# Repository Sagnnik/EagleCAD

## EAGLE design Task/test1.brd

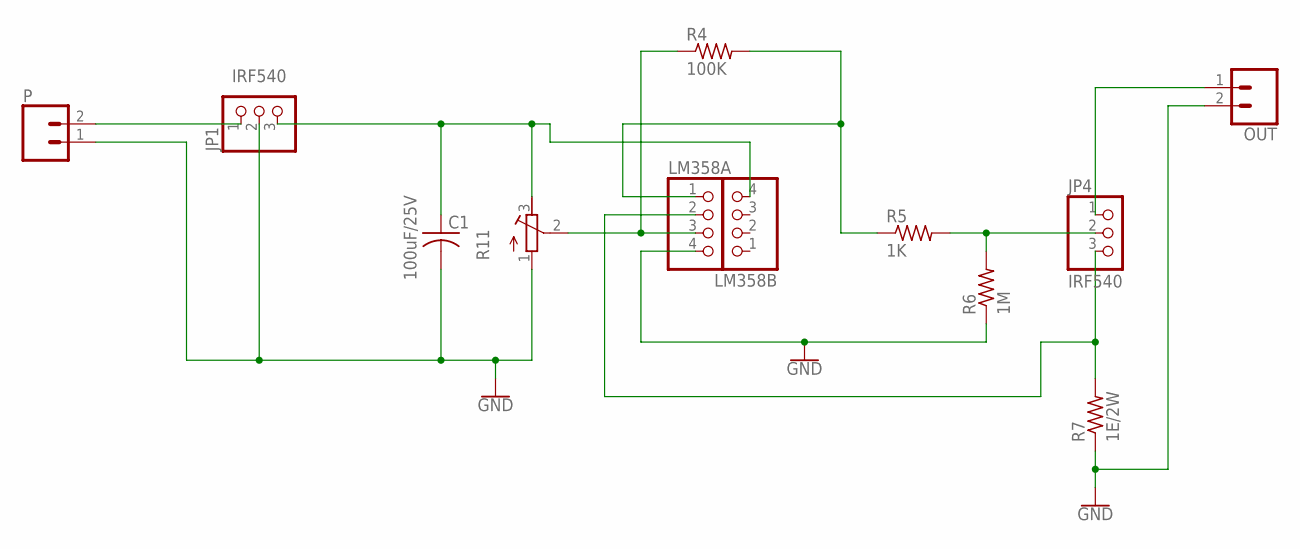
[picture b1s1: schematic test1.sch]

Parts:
C1: 100uF/25V; C025-024X044
JP1, JP4: IRF540; 1X03
LM358A, LM358B: PINHD-1X4; 1X04
OUT: CONN_02; 1X02
P: CONN_02; 1X02
R4: 100K; 0204/5
R5: 1K; 0204/5
R6: 1M; 0204/5
R7: 1E/2W; 0204/5
R11: R-TRIMM3339P; RTRIM3339P

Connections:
GND: C1.2, JP1.2, LM358A.4, OUT.2, P.1, R6.1, R7.1, R11.1 (A)
unnamed: JP1.1, P.2
unnamed: JP4.1, OUT.1
unnamed: JP4.3, LM358A.2, R7.2
unnamed: LM358A.3, R4.1, R11.2 (S)
unnamed: LM358A.1, R4.2, R5.1
unnamed: JP4.2, R5.2, R6.2
O1+: C1.1, JP1.3, LM358B.4, R11.3 (E)

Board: 2 copper layers, 12 parts (0 on the bottom side), 8 nets, no tracks yet.

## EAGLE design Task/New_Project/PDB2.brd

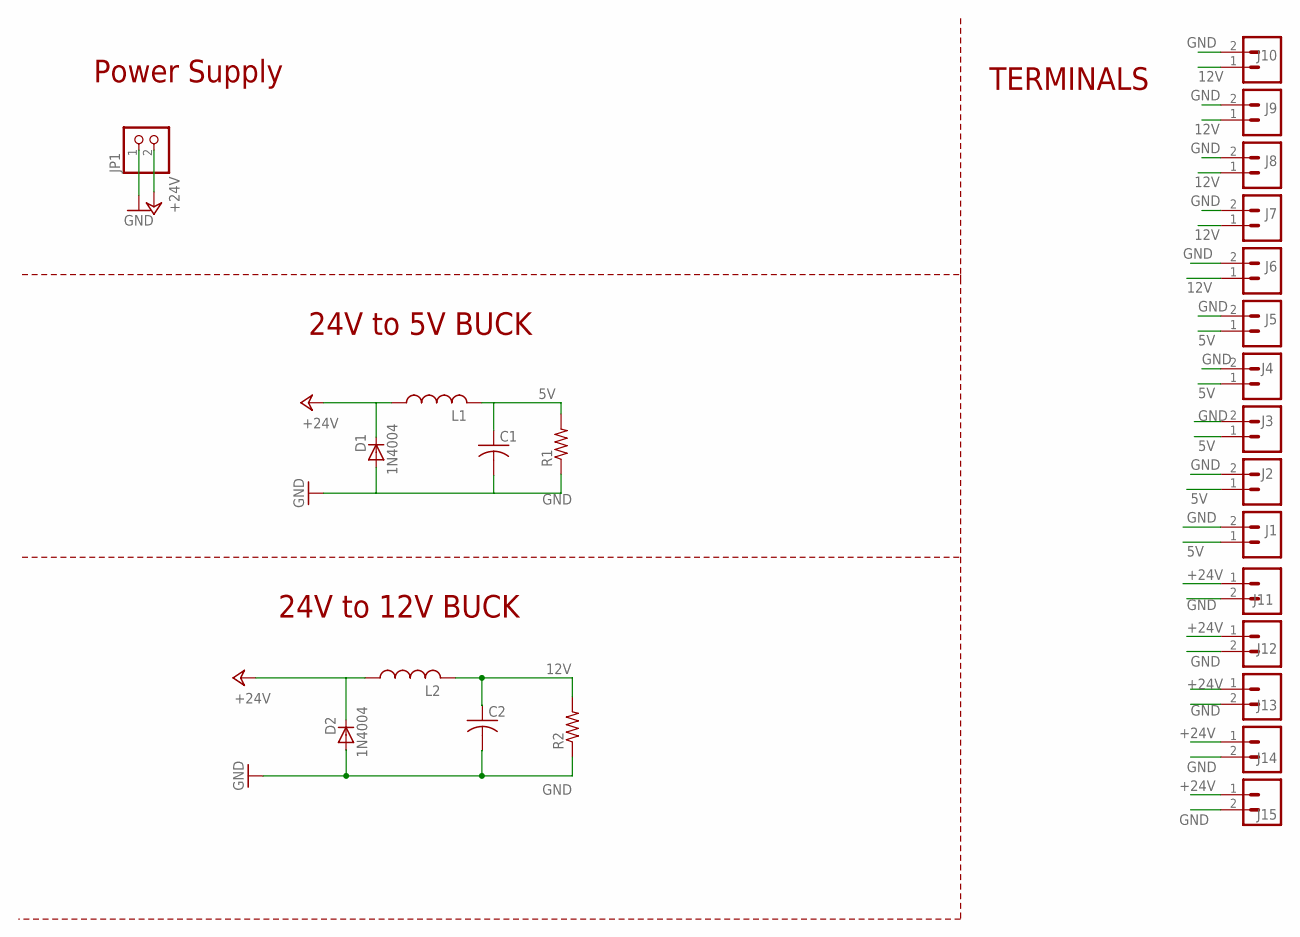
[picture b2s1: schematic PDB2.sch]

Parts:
C1, C2: C-US025-050X050; C025-050X050
D1, D2: 1N4004; DO41-10
J1, J2, J3, J4, J5, J6, J7, J8, J9, J10, J11, J12, J13, J14, J15: CONN_02; 1X02
JP1: PINHD-1X2; 1X02
L1, L2: L-US0207/7; 0207/7
R1, R2: R-US_0207/10; 0207/10

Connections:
5V: C1.1, J1.1, J2.1, J3.1, J4.1, J5.1, L1.2, R1.2
12V: C2.1, J6.1, J7.1, J8.1, J9.1, J10.1, L2.2, R2.2
+24V: D1.C, D2.C, J11.1, J12.1, J13.1, J14.1, J15.1, JP1.2, L1.1, L2.1
GND: C1.2, C2.2, D1.A, D2.A, J1.2, J2.2, J3.2, J4.2, J5.2, J6.2, J7.2, J8.2, J9.2, J10.2, J11.2, J12.2, J13.2, J14.2, J15.2, JP1.1, R1.1, R2.1

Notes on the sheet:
Power Supply
24V to 5V BUCK
24V to 12V BUCK
TERMINALS

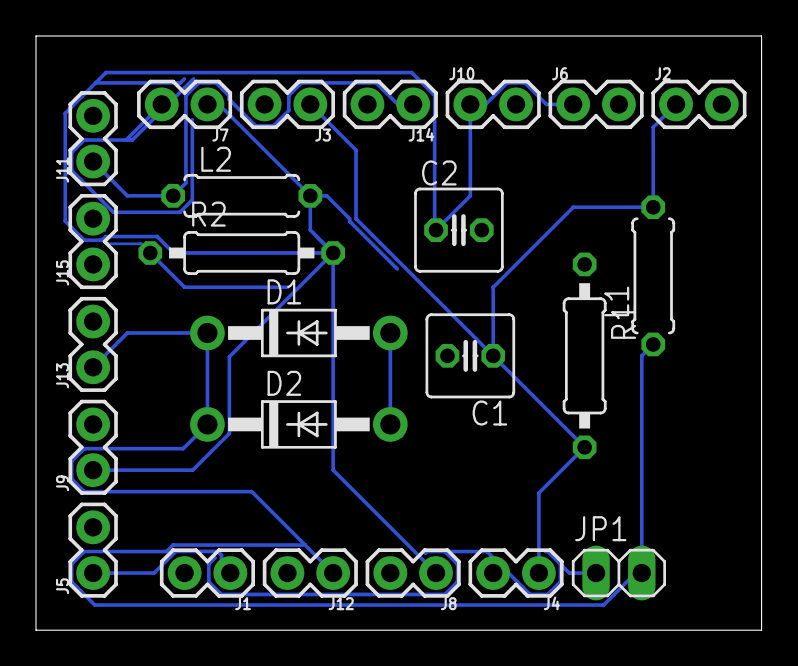
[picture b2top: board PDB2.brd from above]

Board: 2 copper layers, 40.3 x 33.0 mm, 24 parts (0 on the bottom side), 4 nets.

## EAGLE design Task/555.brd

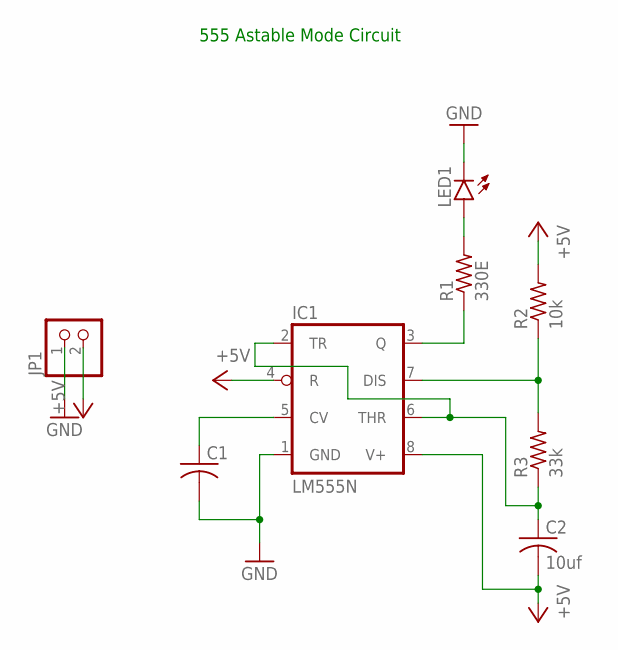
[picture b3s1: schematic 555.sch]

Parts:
C1: C-US025-024X044; C025-024X044
C2: 10uf; C025-024X044
IC1: LM555N; DIL08-ROUND
JP1: PINHD-1X2; 1X02
LED1: LED5MM
R1: 330E; 0204/7
R2: 10k; 0204/7
R3: 33k; 0204/7

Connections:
+5V: C2.2, IC1.4 (R), IC1.8 (V+), JP1.2, R2.2
GND: C1.2, IC1.1 (GND), JP1.1, LED1.K (C)
unnamed: LED1.A, R1.2
unnamed: IC1.3 (Q), R1.1
unnamed: IC1.7 (DIS), R2.1, R3.2
unnamed: C2.1, IC1.2 (TR), IC1.6 (THR), R3.1
unnamed: C1.1, IC1.5 (CV)

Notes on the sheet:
555 Astable Mode Circuit

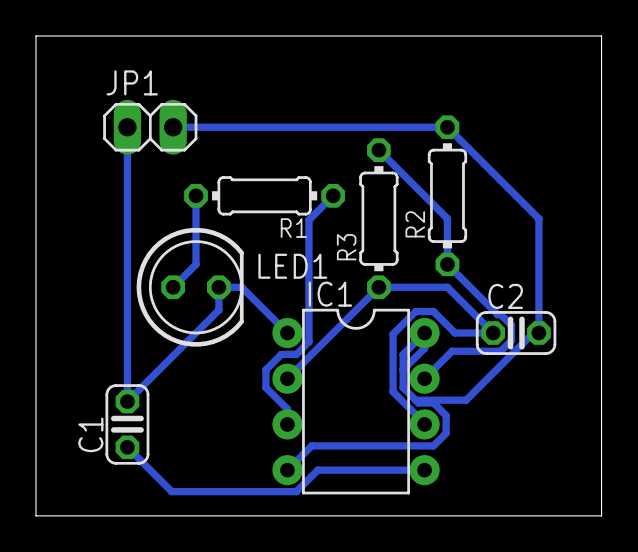
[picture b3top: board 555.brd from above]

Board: 2 copper layers, 31.4 x 26.7 mm, 8 parts (0 on the bottom side), 7 nets.

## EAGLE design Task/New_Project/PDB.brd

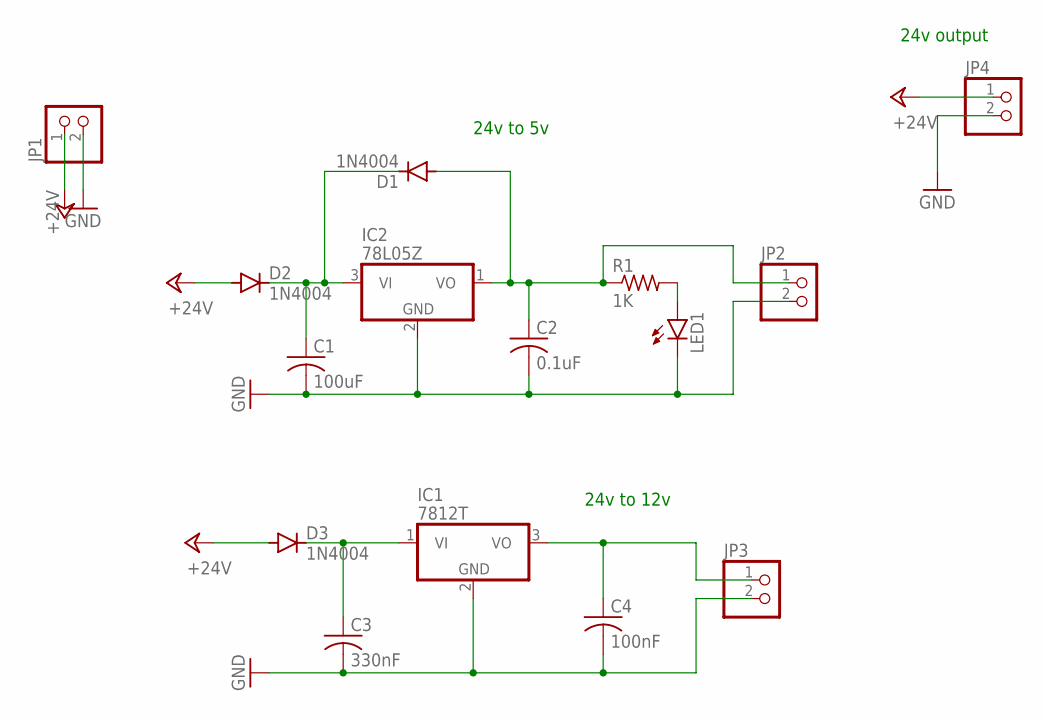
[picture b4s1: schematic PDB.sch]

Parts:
C1: 100uF; C025-024X044
C2: 0.1uF; C025-024X044
C3: 330nF; C025-024X044
C4: 100nF; C025-024X044
D1, D2, D3: 1N4004; DO41-10
IC1: 7812T; TO220H
IC2: 78L05Z; TO92
JP1, JP2, JP3, JP4: PINHD-1X2; 1X02
LED1: LED5MM
R1: 1K; 0204/7

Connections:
+24V: D2.A, D3.A, JP1.1, JP4.1
GND: C1.2, C2.2, C3.2, C4.2, IC1.2 (GND), IC2.2 (GND), JP1.2, JP2.2, JP3.2, JP4.2, LED1.K (C)
unnamed: C3.1, D3.C, IC1.1 (VI)
unnamed: C1.1, D1.C, D2.C, IC2.3 (VI)
unnamed: C2.1, D1.A, IC2.1 (VO), JP2.1, R1.1
unnamed: C4.1, IC1.3 (VO), JP3.1
unnamed: LED1.A, R1.2

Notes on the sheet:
24v to 5v
24v to 12v
24v output

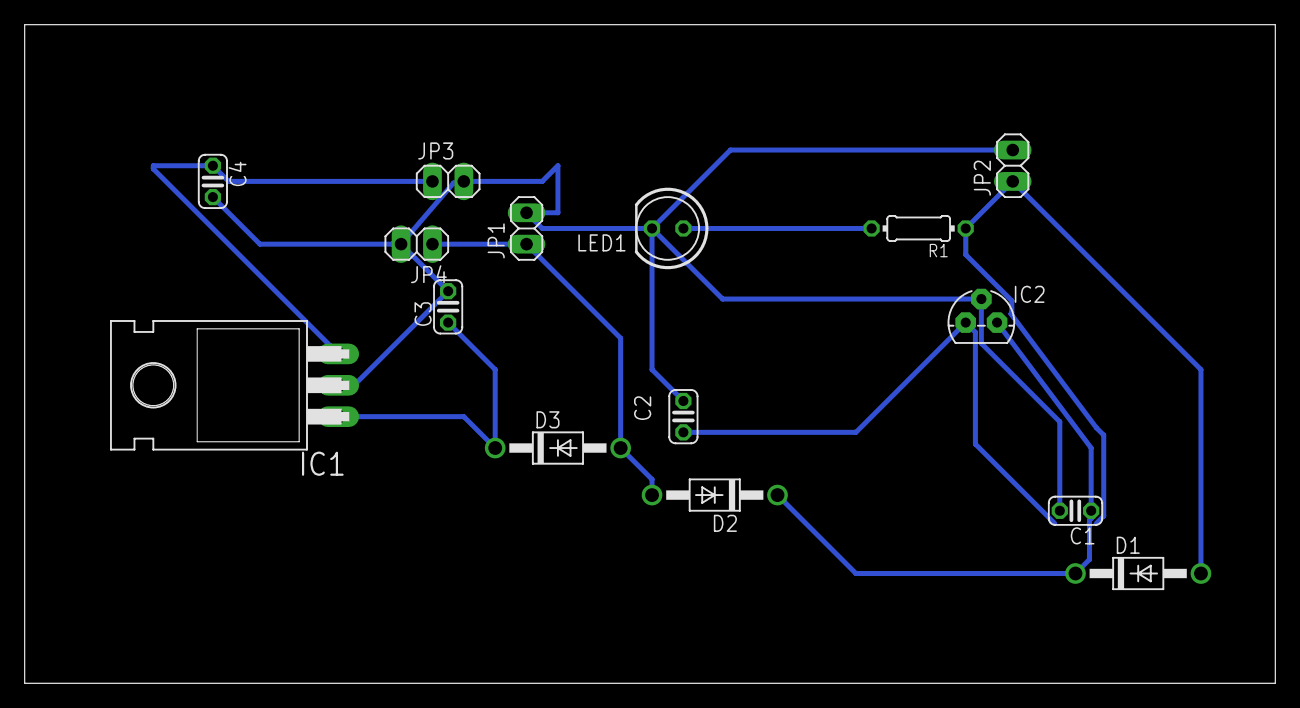
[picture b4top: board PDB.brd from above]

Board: 2 copper layers, 101.3 x 53.3 mm, 15 parts (0 on the bottom side), 7 nets.

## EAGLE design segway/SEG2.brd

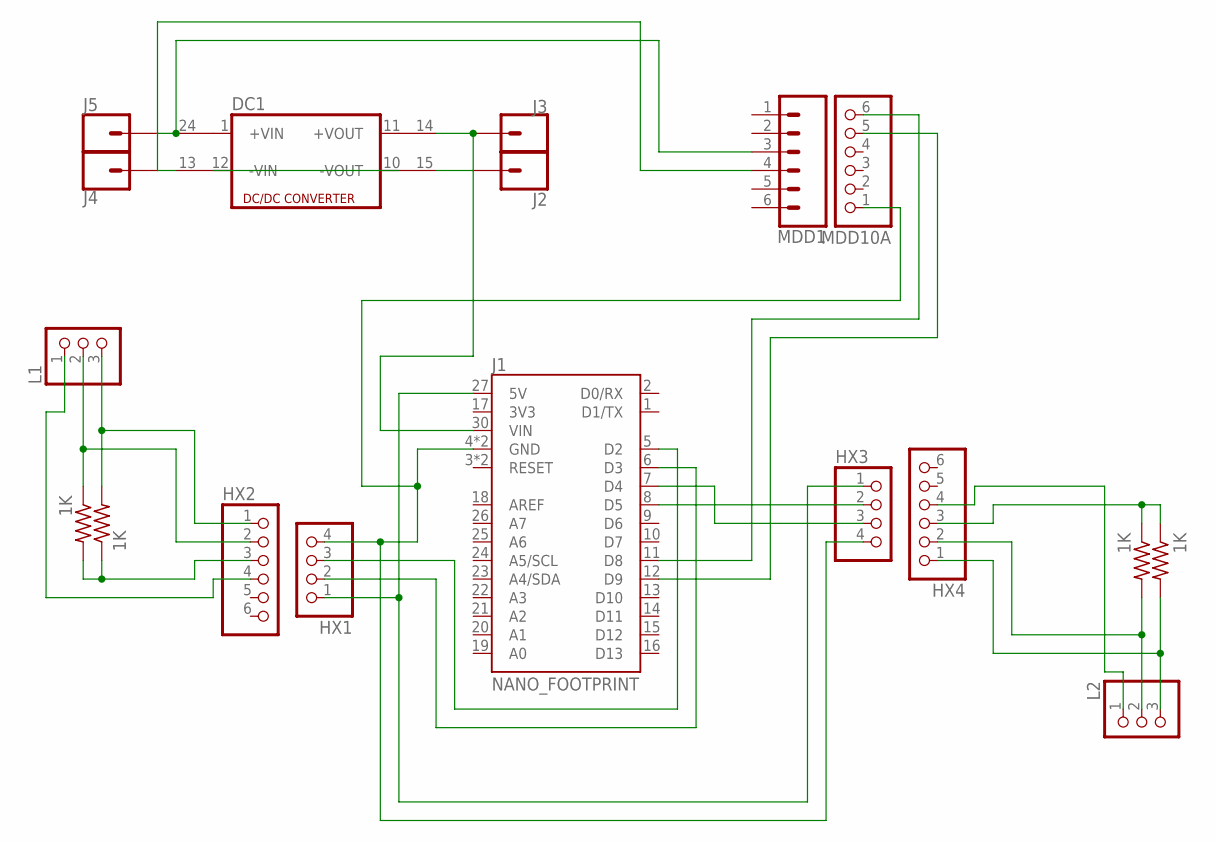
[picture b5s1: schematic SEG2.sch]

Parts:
DC1: DC213R; CMK
HX1, HX3: PINHD-1X4; 1X04
HX2, HX4: PINHD-1X6; 1X06
J1: NANO_FOOTPRINT; NANO
J2, J3, J4, J5: CONN_01; 1X01
L1, L2: PINHD-1X3; 1X03
MDD1: CONN_06LOCK; 1X06_LOCK
MDD10A: PINHD-1X6; 1X06
R1, R2, R3, R4: 1K; 0204/7

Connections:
unnamed: HX1.4, HX3.4, J1.4 (GND), J1.29 (GND), MDD10A.1
unnamed: HX1.3, J1.5 (D2)
unnamed: HX1.2, J1.6 (D3)
unnamed: HX1.1, HX3.1, J1.27 (5V)
unnamed: HX2.3, R1.1, R2.2
unnamed: HX3.3, J1.7 (D4)
unnamed: HX3.2, J1.8 (D5)
unnamed: HX2.2, L1.2, R2.1
unnamed: HX2.4, L1.1
unnamed: HX2.1, L1.3, R1.2
unnamed: HX4.1, L2.3, R3.2
unnamed: HX4.2, L2.2, R4.2
unnamed: DC1.24 (+VIN1), J4.1, MDD1.3
unnamed: HX4.3, R3.1, R4.1
unnamed: HX4.4, L2.1
unnamed: DC1.14 (+VOUT1), J1.30 (VIN), J2.1
unnamed: DC1.10 (-VOUT), DC1.12 (-VIN)
unnamed: DC1.13 (-VIN1), J5.1, MDD1.4
unnamed: DC1.15 (-VOUT1), J3.1
unnamed: J1.11 (D8), MDD10A.6
unnamed: J1.12 (D9), MDD10A.5

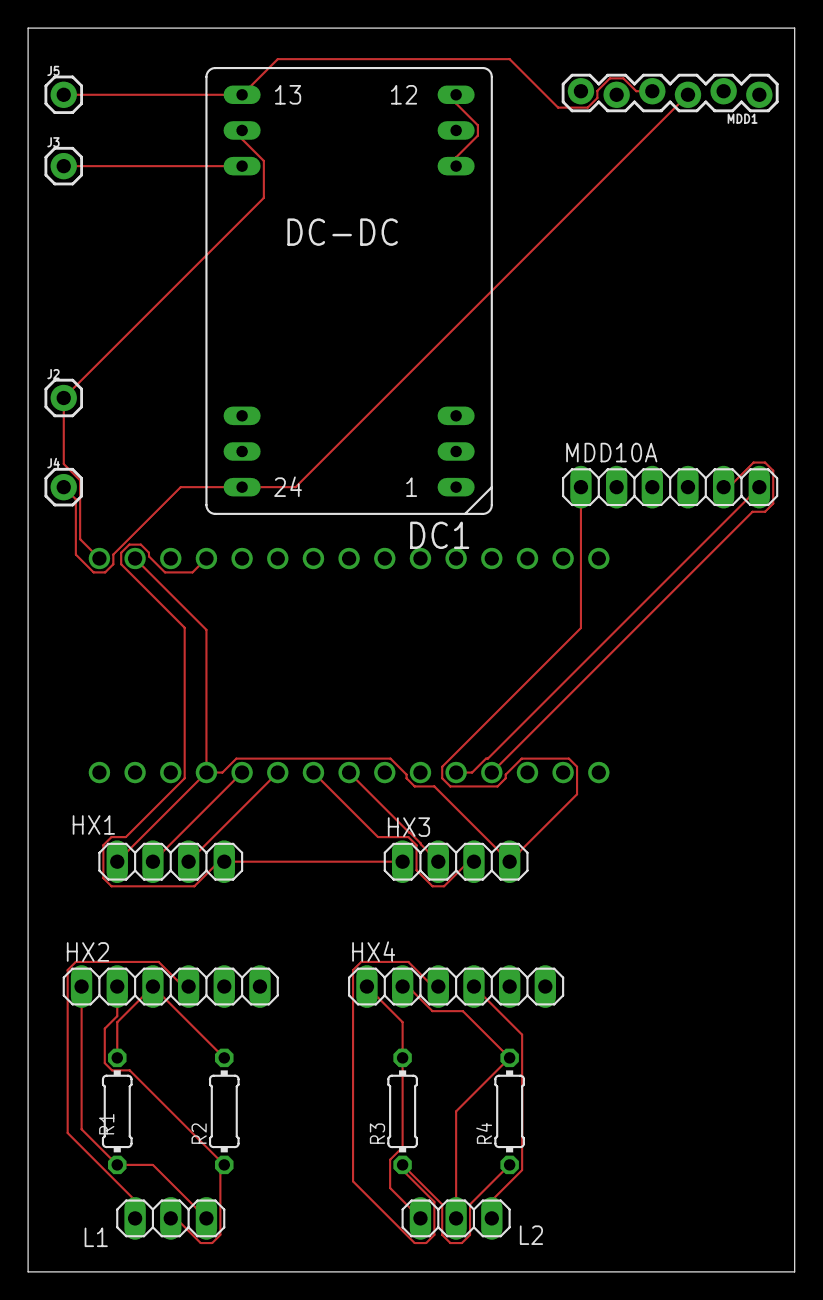
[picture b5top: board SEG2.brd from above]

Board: 2 copper layers, 54.6 x 88.6 mm, 18 parts (0 on the bottom side), 21 nets.

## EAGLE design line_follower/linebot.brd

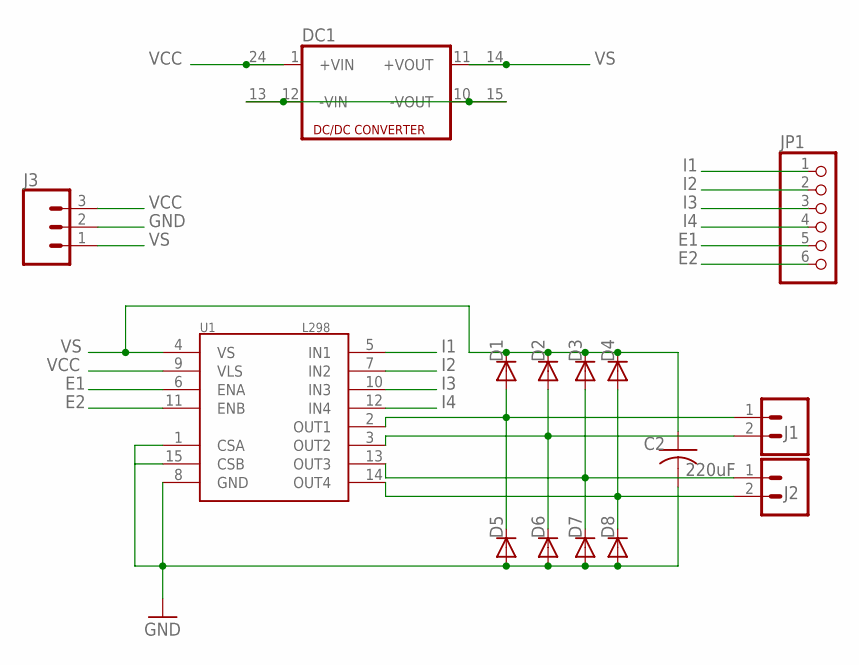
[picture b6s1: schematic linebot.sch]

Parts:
C2: 220uF; C025-024X044
D1, D2, D3, D4, D5, D6, D7, D8: 1N4004; DO41-10
DC1: DC213R; CMK
J1, J2: CONN_02; 1X02
J3: 455-1750-1-ND; 1X03
JP1: PINHD-1X6; 1X06
U1: L298; MULTIWATT15

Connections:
E1: JP1.5, U1.6 (ENA)
E2: JP1.6, U1.11 (ENB)
GND: C2.2, D5.A, D6.A, D7.A, D8.A, J3.2, U1.1 (CSA), U1.8 (GND), U1.15 (CSB)
I1: JP1.1, U1.5 (IN1)
I2: JP1.2, U1.7 (IN2)
I3: JP1.3, U1.10 (IN3)
I4: JP1.4, U1.12 (IN4)
unnamed: D1.A, D5.C, J1.1, U1.2 (OUT1)
unnamed: D2.A, D6.C, J1.2, U1.3 (OUT2)
unnamed: D3.A, D7.C, J2.1, U1.13 (OUT3)
unnamed: D4.A, D8.C, J2.2, U1.14 (OUT4)
unnamed: DC1.10 (-VOUT), DC1.12 (-VIN), DC1.13 (-VIN1), DC1.15 (-VOUT1)
VCC: DC1.1 (+VIN), DC1.24 (+VIN1), J3.3, U1.9 (VLS)
VS: C2.1, D1.C, D2.C, D3.C, D4.C, DC1.11 (+VOUT), DC1.14 (+VOUT1), J3.1, U1.4 (VS)

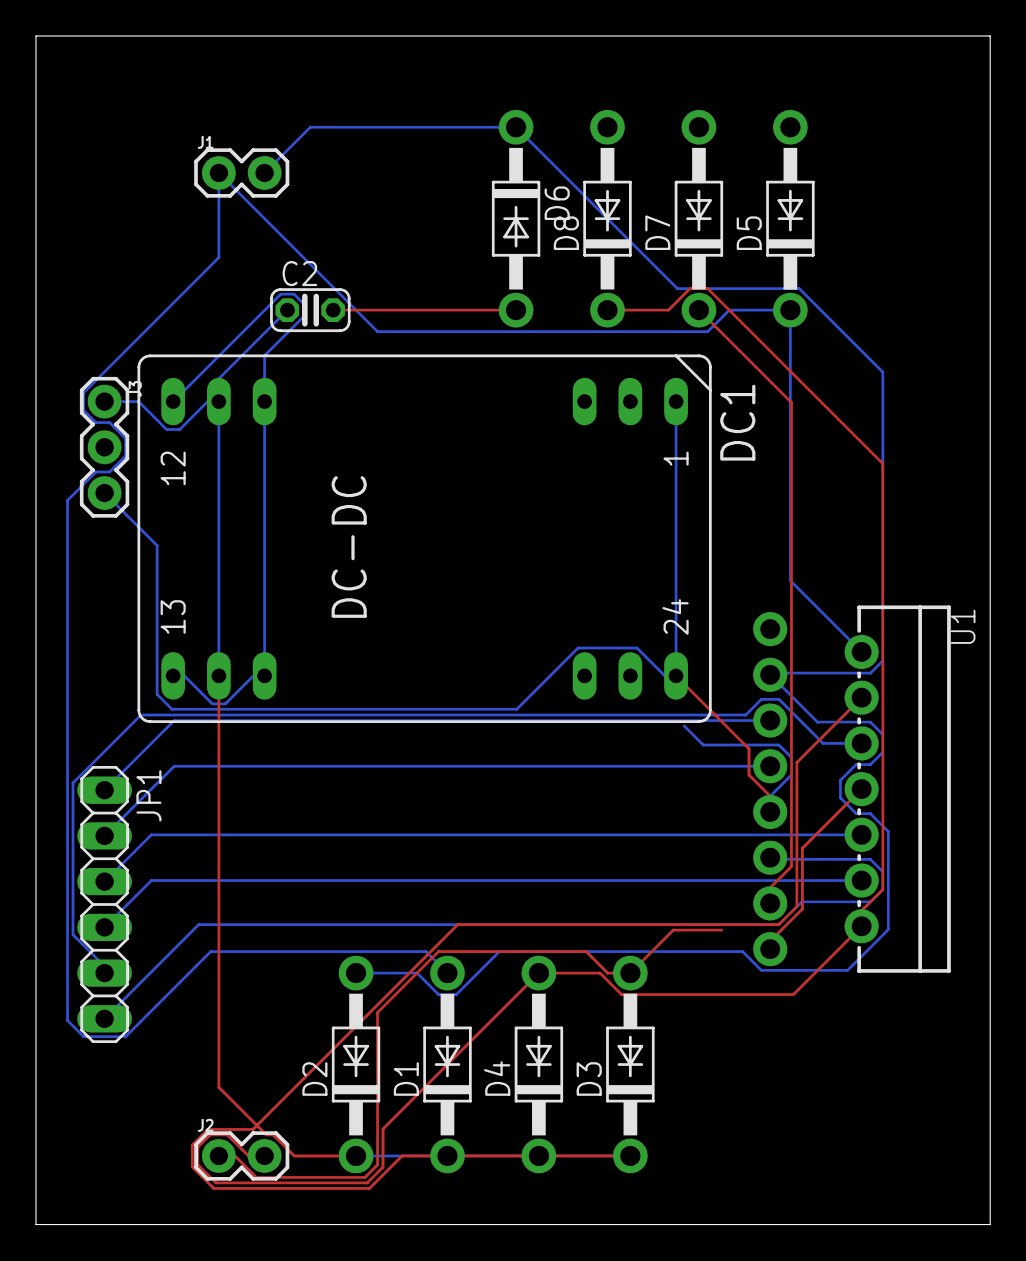
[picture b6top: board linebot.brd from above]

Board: 2 copper layers, 53.0 x 66.0 mm, 15 parts (0 on the bottom side), 14 nets.

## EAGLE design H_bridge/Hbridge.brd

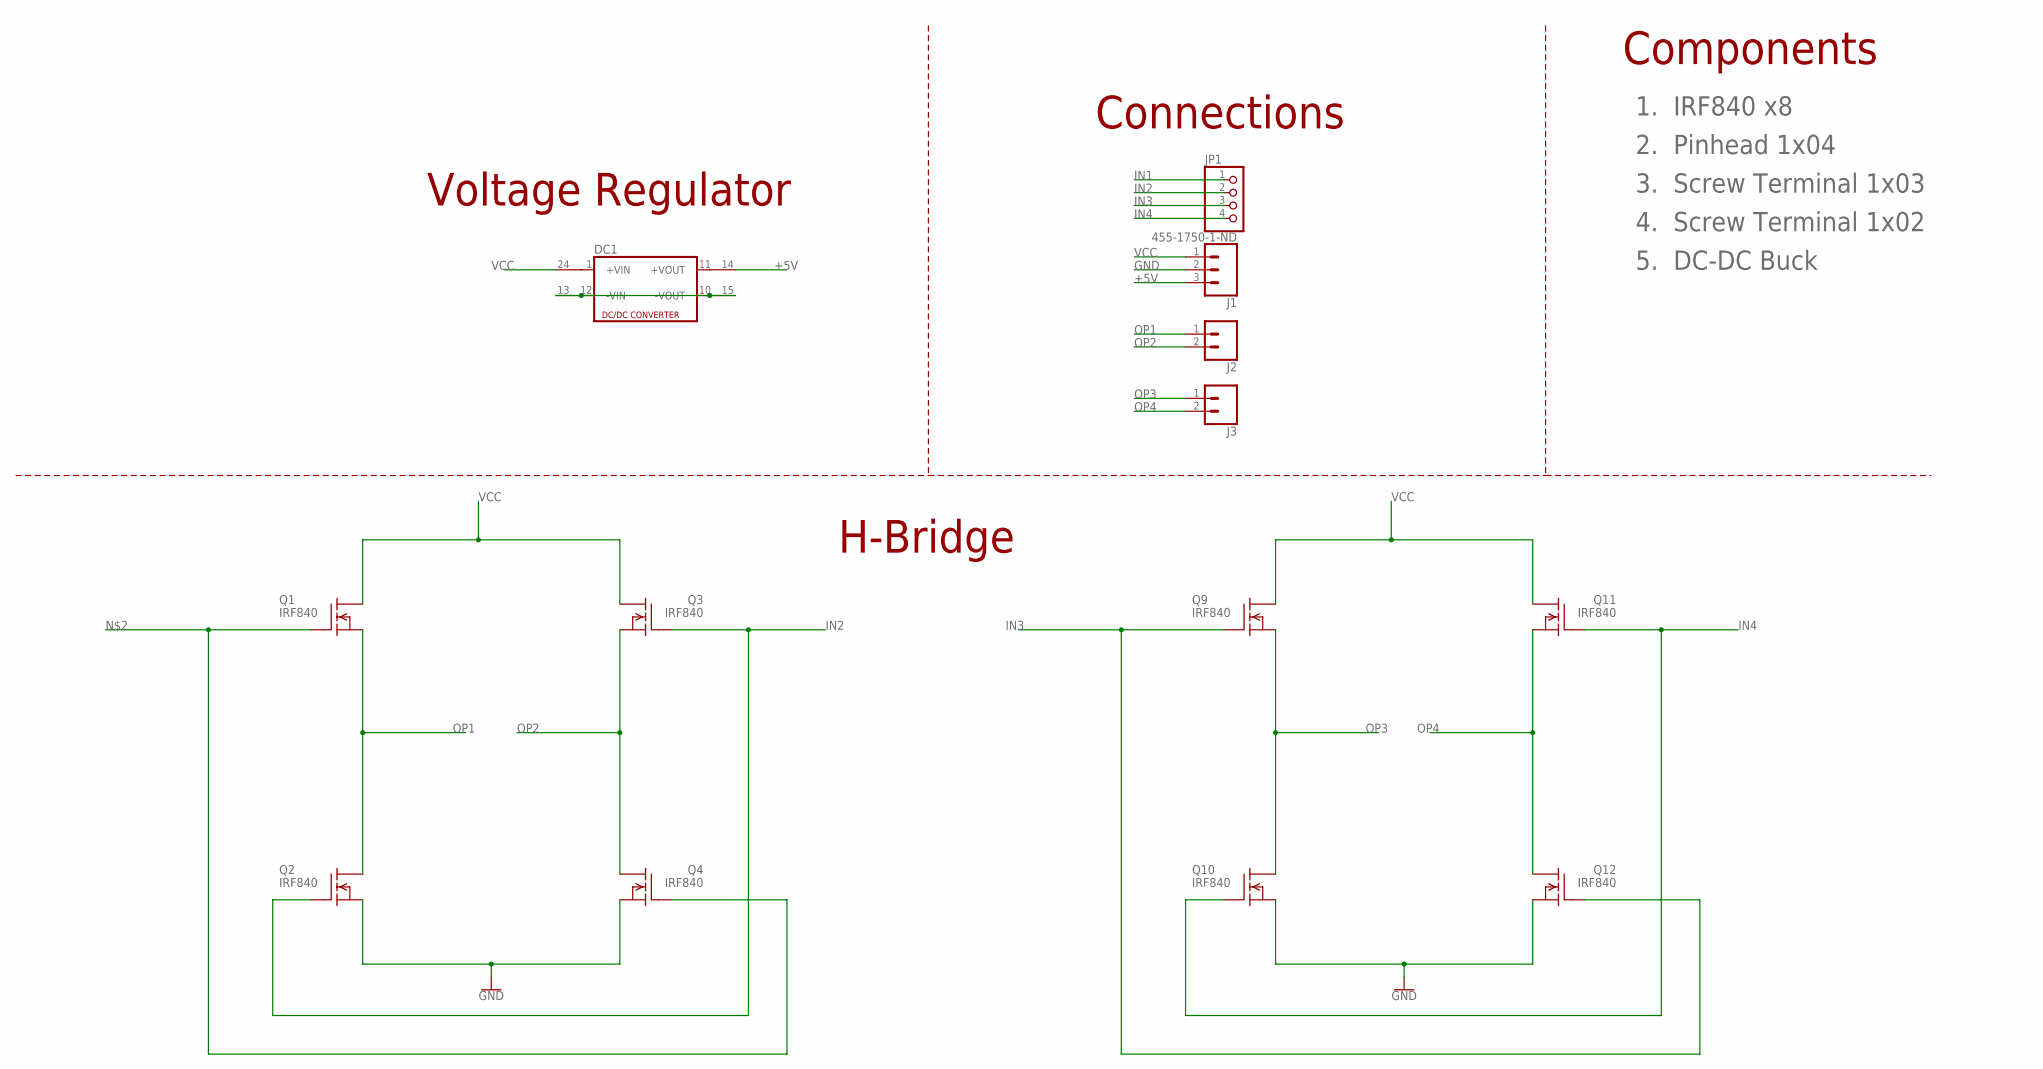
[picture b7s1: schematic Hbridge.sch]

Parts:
DC1: DC213R; CMK
J1: 455-1750-1-ND; 1X03
J2, J3: CONN_02; 1X02
JP1: PINHD-1X4; 1X04
Q1, Q2, Q3, Q4, Q9, Q10, Q11, Q12: IRF840; TO220

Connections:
+5V: DC1.14 (+VOUT1), J1.3
GND: J1.2, Q2.3 (S), Q4.3 (S), Q10.3 (S), Q12.3 (S)
IN1: JP1.1
IN2: JP1.2, Q2.1 (G), Q3.1 (G)
IN3: JP1.3, Q9.1 (G), Q12.1 (G)
IN4: JP1.4, Q10.1 (G), Q11.1 (G)
unnamed: Q1.1 (G), Q4.1 (G)
unnamed: DC1.10 (-VOUT), DC1.12 (-VIN), DC1.13 (-VIN1), DC1.15 (-VOUT1)
OP1: J2.1, Q1.3 (S), Q2.2 (D)
OP2: J2.2, Q3.3 (S), Q4.2 (D)
OP3: J3.1, Q9.3 (S), Q10.2 (D)
OP4: J3.2, Q11.3 (S), Q12.2 (D)
VCC: DC1.24 (+VIN1), J1.1, Q1.2 (D), Q3.2 (D), Q9.2 (D), Q11.2 (D)

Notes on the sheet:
Voltage Regulator
Connections
H-Bridge
Components
1. IRF840 x8
2. Pinhead 1x04
3. Screw Terminal 1x03
4. Screw Terminal 1x02
5. DC-DC Buck

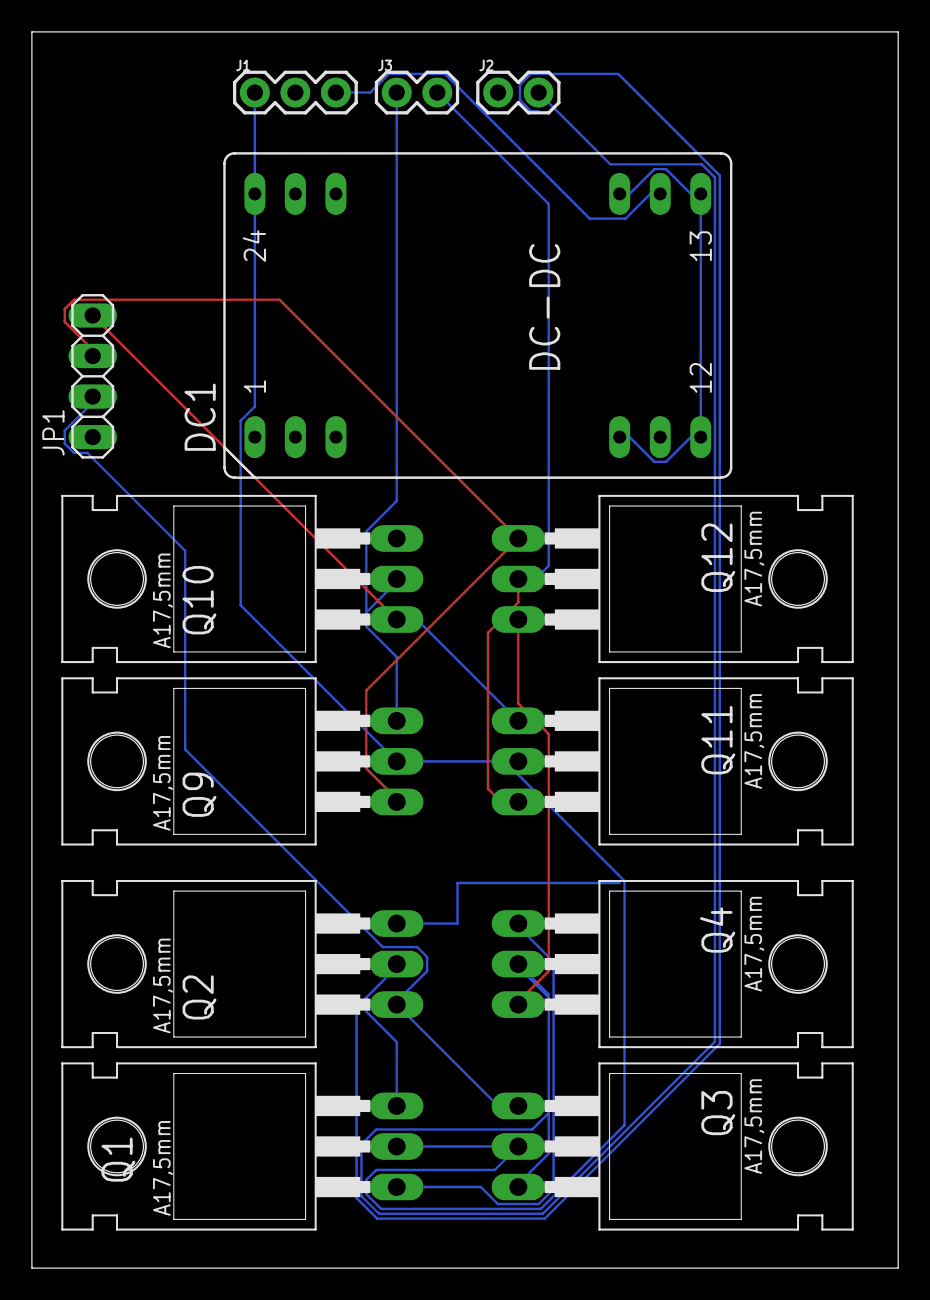
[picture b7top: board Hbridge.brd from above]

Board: 2 copper layers, 54.3 x 77.5 mm, 13 parts (0 on the bottom side), 12 nets.

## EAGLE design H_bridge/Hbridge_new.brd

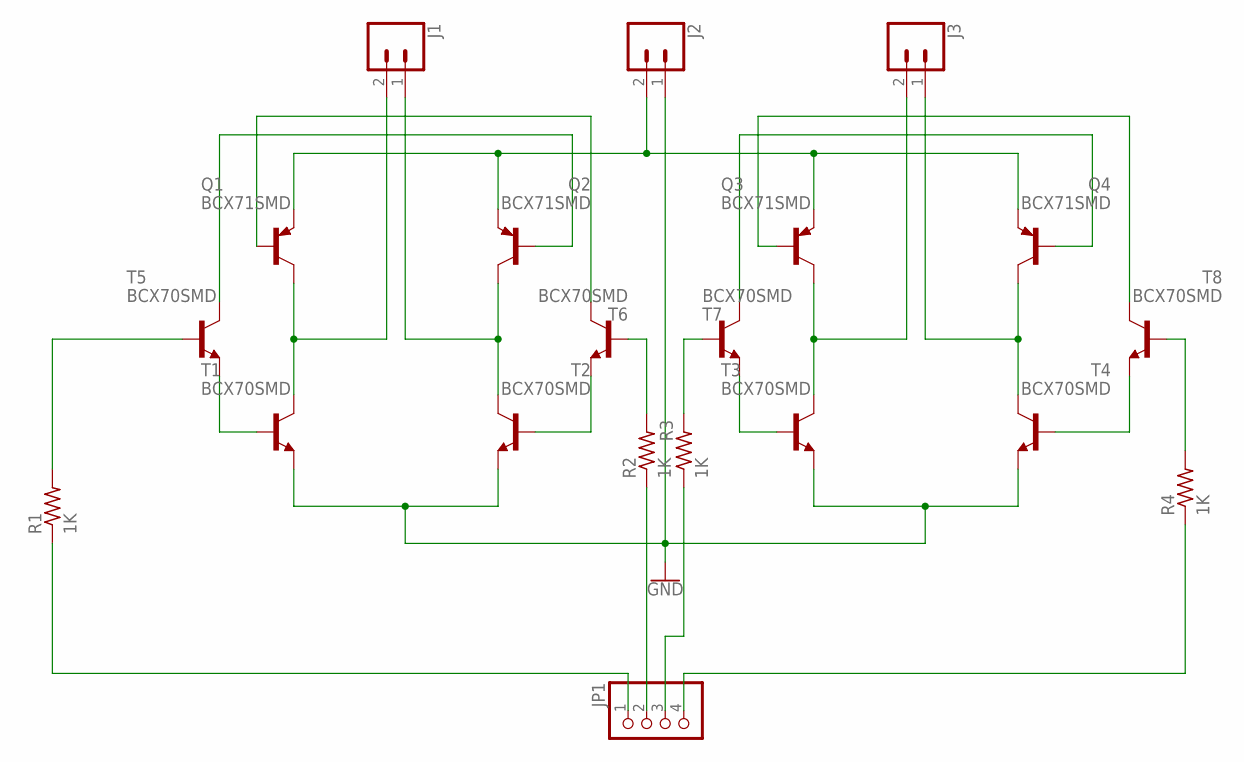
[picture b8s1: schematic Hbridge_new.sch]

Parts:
J1, J2, J3: CONN_02-JST-2MM-SMT; JST-2-SMD
JP1: PINHD-1X4; 1X04
Q1, Q2, Q3, Q4: BCX71SMD; SOT23
R1, R2, R3, R4: 1K; M0805
T1, T2, T3, T4, T5, T6, T7, T8: BCX70SMD; SOT23

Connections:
GND: J2.1 (2), T1.2 (E), T2.2 (E), T3.2 (E), T4.2 (E)
unnamed: Q2.1 (B), T5.3 (C)
unnamed: J1.1 (2), Q2.3 (C), T2.3 (C)
unnamed: Q1.1 (B), T6.3 (C)
unnamed: J1.2 (1), Q1.3 (C), T1.3 (C)
unnamed: JP1.1, R1.1
unnamed: JP1.2, R2.1
unnamed: T1.1 (B), T5.2 (E)
unnamed: T2.1 (B), T6.2 (E)
unnamed: J2.2 (1), Q1.2 (E), Q2.2 (E), Q3.2 (E), Q4.2 (E)
unnamed: J3.1 (2), Q4.3 (C), T4.3 (C)
unnamed: J3.2 (1), Q3.3 (C), T3.3 (C)
unnamed: JP1.3, R3.1
unnamed: JP1.4, R4.1
unnamed: Q4.1 (B), T7.3 (C)
unnamed: Q3.1 (B), T8.3 (C)
unnamed: T3.1 (B), T7.2 (E)
unnamed: T4.1 (B), T8.2 (E)
unnamed: R1.2, T5.1 (B)
unnamed: R2.2, T6.1 (B)
unnamed: R3.2, T7.1 (B)
unnamed: R4.2, T8.1 (B)

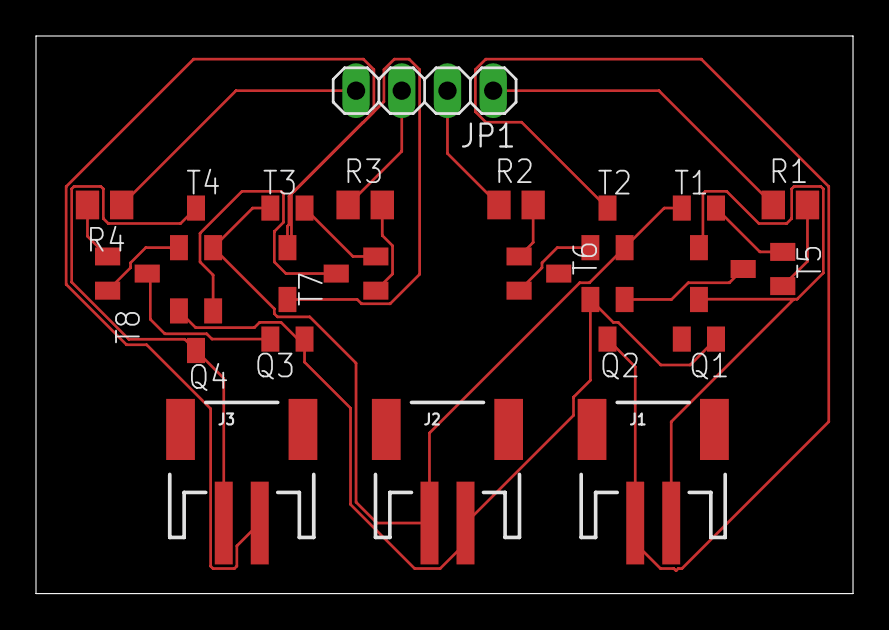
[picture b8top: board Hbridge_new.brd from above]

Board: 2 copper layers, 45.4 x 31.0 mm, 20 parts (0 on the bottom side), 22 nets.

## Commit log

2022-08-16 Custom Controller Design
2022-08-16 H Bridge Motor Driver PDB design
2022-08-16 Line Following Robot PCB designs
2022-08-16 PCB designs for both R1 & R2 bot
2022-08-16 Roomba themed project PCB designs
2022-08-16 Segway themed project PCB designs
2022-08-16 Tasks at RM

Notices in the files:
parts and their libraries:
SparkFun-Connectors: Licensing: Creative Commons ShareAlike 4.0 International - https://creativecommons.org/licenses/by-sa/4.0
